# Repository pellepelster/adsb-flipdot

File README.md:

# ADS-B FlipDot

As an avid aviation nerd who happens to live almost exactly on the extended centerline of EDDH's RWY 15, I have a
constant stream of airplanes flying over my house. And although EDDH is a small airport that is rarely visited by
exciting aircraft, I still often step outside when I hear a plane approaching to see what is coming.

I am also a nerd and fully aware of apps like Flightradar24, but I wanted a dedicated device to show me what's flying
overhead, one that gives off some airport vibes instead of a boring mobile phone screen.

https://github.com/user-attachments/assets/cd77bf14-a6f2-4459-a4ed-02358a0cf8c3

## The plan

### ADS-B data

I do not want to rely on or pay for an API to run the displays. The data that Flightradar24 is based on can be received<video src="video/adsb-flipdot-video-embedded.mp4" controls muted playsinline width="100%"></video>
freely using an RTL2832U-based DVB-T stick, which can be tuned far beyond the standard television bands, up to
1090 MHz, to receive the ADS-B data the aircraft are broadcasting.

Looking into the [ADS-B message structure](https://mode-s.org/1090mhz/index.html), the most important information for
my use case is the current position as latitude and longitude, as well as the current heading and altitude.

Using this information I can create a virtual box around my house, catching all aircraft that cross this box at a
certain altitude and filtering out all other irrelevant traffic that is crossing overhead.

### Display

In an ideal world I would like to use a [split-flap](https://en.wikipedia.org/wiki/Split-flap_display) display like the
ones that were widely used at airports (some, e.g. EDDF, still have them). Looking at the prices for original modules
or even DIY alternatives, those are completely out of my price range for this project.

Luckily, the technology that replaced them is much more accessible.
[Flip-disc (or flip-dot)](https://en.wikipedia.org/wiki/Flip-disc_display) displays not only make a nice clicking noise
resembling that of split-flap displays, they can also show arbitrary glyphs. They were widely used as destination signs
in buses and are thus readily available on second-hand platforms.

### Processing

Because the data from ADS-B comes in via USB and needs a bit of processing power and driving the matrix display requires
quite a few I/O lines to address and drive the dots, a old Raspberry PI is a perfect fit for the task. I also wanted to
use this opportunity to get to know Rust a little bit closer, and there is a
nice [crate](https://docs.rs/rs1090/latest/rs1090/)
available that already can decode ADS-B messages.

## Implementation

### Display

#### The dots

The Mobitec is built from an array of small hinged discs with different colors on each side, that show as black or
yellow forming the dots.

The displays are chainable (up to 6 i Think). To understand how to drive them correctly without risking damage, we need to 
look a little bit deeper into how they work internally.

Each disc carries a small bar magnet along its length and sits above the two poles of a U-shaped iron core with a
coil wound around it. A short current pulse through the coil magnetises the core. Its poles pull the opposite ends of
the disc magnet, and the disc turns until each end of the magnet faces the opposite pole. Reversing the current swaps
the poles, and the disc turns half a turn to show its other face. After the pulse the disc magnet holds on to the iron
core, so the disc keeps its position without power and the coil only needs a short pulse to flip it.

The Mobitec has an 26 pin input header, allows to select each individual dot, and also to turn it back and forth.

#### Dot selection

A dot is picked by two 5 bit addresses, one for the row (pins 5, 7, 6, 8 and 9) and one for the column (pins 13 to
17). The panel does not decode them as plain numbers. The two upper bits pick one of several decoder chips, each of
which drives a group of seven lines, and the three lower bits pick one line of that group. A value of 0 in the lower
bits selects nothing, so every eighth address (0, 8, 16, 24) is skipped:

| Rows  | Address | Columns | Address |
|-------|---------|---------|---------|
| 1–7   | 1–7     | 1–7     | 1–7     |
| 8–14  | 9–15    | 8–14    | 9–15    |
| 15–16 | 17–18   | 15–21   | 17–23   |
|       |         | 22–28   | 25–31   |

For example, the dot in row 10, column 20:

|        | Number | Group | Line | Address    | Pins high  | Pins low |
|--------|--------|-------|------|------------|------------|----------|
| Row    | 10     | 1     | 3    | 11 = 01011 | 5, 7, 8    | 6, 9     |
| Column | 20     | 2     | 6    | 22 = 10110 | 14, 15, 17 | 13, 16   |

#### Flipping a dot

Once a dot is selected, three more signals decide what happens to it. Each row has two lines, one that can only feed
current into its coils and one that can only drain it, separated by a diode at every dot. The column has a single line
that can be connected to the coil supply or to ground.

- **Direction (pin 18)** picks which way the current runs through the coil. Low connects the row to the coil supply
  and the column to ground, and the dot turns yellow. High does the opposite, and the dot turns black.
- **Row enable (pin 11 ROW-LOW, pin 10 ROW-HIGH)** switches the row side on. Use pin 11 together with pin 18 low and
  pin 10 together with pin 18 high, and never set both at the same time.
- **Select (pin 19)** fires the dot. Current only flows while it is high, so a pulse of about 190 µs flips the dot.
  Keep it short: a coil that stays energised overheats.

So one dot is flipped in four steps: set the address and the direction, enable the row, pulse pin 19 and switch the
row off again before the next dot.

### Raspberry HAT

Dot selection and configuration of the flipping direction expects 5v logic, and although the Raspberry Pi has plenty of GPIO pins, they all only deliver 3.3v. To be able to drive the display via Raspberry Pi I designed small adapter HAT, that runs the GPIO pins through some levels shifters to deliver the correct 5v. 

All needed design files to manufacture the board are under `./pcb`. Once populated with three levels shifters and a few capacitators to smooth out the current when selecting and switching dots (see BOM at [flipdot-hat-assembly-bom.csv](pcb/assembly/flipdot-hat-assembly-bom.csv)) the HAT can be directly stacked on the Raspberry Pi GPIO pins, and connected to the display via a ribbon cable.

### Software

The software `adsb-flipdot` uses a virtual double-buffered Matrix display. Once new content is written the virtual display computes the diff on yellow/black dots from the previous content to avoid re-drawing the full matrix every time, which would be too time consuming. When no display is attached, the virtual display is written to the console to enable easier debugging.

```shell
./adsb-flipdot debug

Diagnostic tools

Usage: adsb-flipdot debug <COMMAND>

Commands:
  dump       Print every received Mode S / ADS-B frame to the console
  record     Save every received frame to a JSON lines file, for replay with --device-record-file
  all        Show a continuously updated table with one row per aircraft
  filter     Show aircraft passing a rectangle around a point, below an altitude
  flipdot    Preview text as dots, the way the flipdot panel will show it
  pi         Switch the signals of the adapter board on the Raspberry Pi by hand
  clear      Turn every dot of the panels to its dark side
  pattern    Show test patterns one after another, until stopped
  templates  List the codes that can be used in `live --template`
  help       Print this message or the help of the given subcommand(s)
```

The default lat/long parameters are tuned so the flight info is shown once the aircraft passes my house, this is how it looks in real life

https://github.com/user-attachments/assets/cd77bf14-a6f2-4459-a4ed-02358a0cf8c3

## Building and deploying

All tasks to build and deploy solutions are documented and executable via [mise](https://mise.jdx.dev)

```shell
 mise t
Name           Description
ansible        Set up a Raspberry Pi over SSH (udev rule + DVB blacklist), e.g. `mise ansible 10.42.0.112`
build          Build the project (debug)
build:pi       Cross-compile static release binaries for 64-bit and 32-bit Raspberry Pi (needs Docker)
build:pi:32    Cross-compile a static release binary for 32-bit Raspberry Pi, e.g. the Pi 2 (needs Docker)
build:pi:64    Cross-compile a static release binary for 64-bit Raspberry Pi (needs Docker)
check          Format check + clippy + tests
clean          Remove build artifacts
fmt            Format sources
fmt:check      Verify formatting
lint           Run clippy with warnings as errors
pcb:board      Place, autoroute and pour the board (build_board.py -> .kicad_pcb)
pcb:drc        Run DRC (-> pcb/drc.json)
pcb:generate   Regenerate all generated PCB files (board, DRC, gerbers, assembly, renders)
pcb:gerbers    Export gerbers and drill files (-> pcb/gerbers/)
pcb:placement  Export the placement file (-> pcb/assembly/)
pcb:render     Render pcb/top.png and pcb/bottom.png
pcb:zip        Pack pcb/gerbers/ and pcb/assembly/ into the upload zips
release        Build the project (release)
run            Run adsb-flipdot (release build), e.g. `mise run run debug dump`
setup-udev     Install udev rule + DVB blacklist for the RTL2832U dongle (needs sudo)
test           Run tests
```

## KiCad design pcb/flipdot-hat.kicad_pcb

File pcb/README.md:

# Flip-dot adapter board

A Raspberry Pi HAT that connects the Pi to the 26-pin header of a Mobitec
flip-dot panel. The board is generated by `build_board.py`.

The signals, the panel pinout, the addresses and how to switch a dot are
described in [docs/mobitec/README.md](../docs/mobitec/README.md).

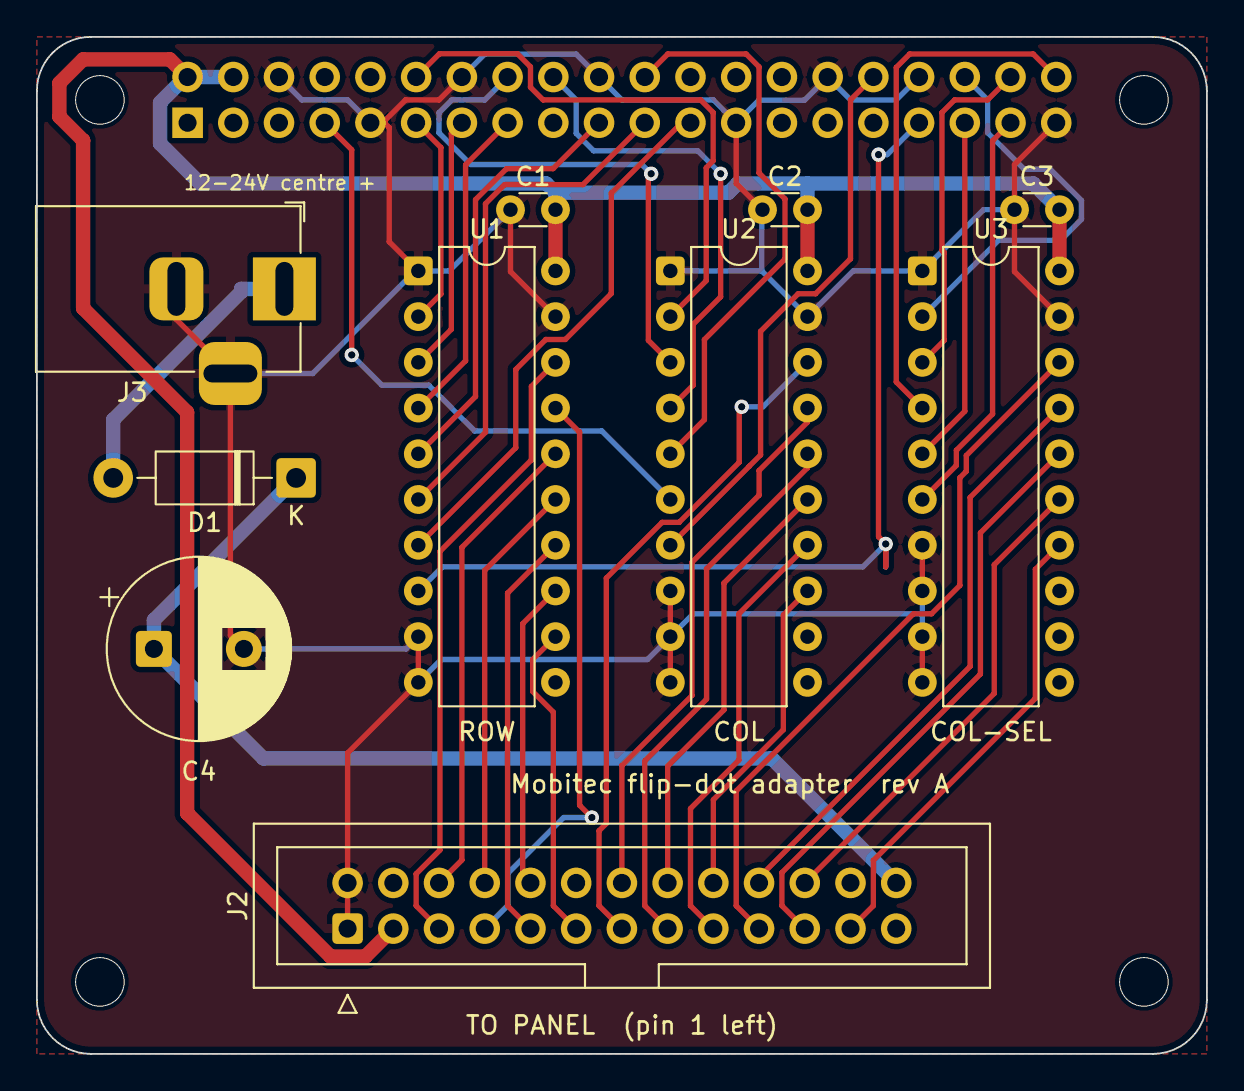
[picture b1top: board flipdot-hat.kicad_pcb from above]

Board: 2 copper layers, 65.0 x 56.5 mm, 15 parts (1 on the bottom side), 40 nets.

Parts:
C1, C2, C3: 100n; C_Disc_D3.0mm_W1.6mm_P2.50mm
C4: 470u 35V; CP_Radial_D10.0mm_P5.00mm
D1: 1N5819; D_DO-41_SOD81_P10.16mm_Horizontal
H1, H2, H3, H4: M2.5; MountingHole_2.7mm_M2.5
J1: Pi socket 2x20; PinSocket_2x20_P2.54mm_Vertical
J2: Panel 2x13 IDC; IDC-Header_2x13_P2.54mm_Vertical
J3: 12-24V 5.5x2.1 centre +; BarrelJack_Horizontal
U1, U2, U3: 74HCT541; DIP-20_W7.62mm

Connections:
+5V: C1.1, C2.1, C3.1, J1.2, J1.4, J2.3, U1.20, U2.20, U3.20
+12V: C4.1, D1.1, J2.26
COL0: J2.13, U2.18
COL1: J2.14, U2.17
COL2: J2.15, U2.16
COL3: J2.16, U2.15
COL4: J2.17, U2.14
COL-H/L: J2.18, U2.13
COL-SEL0: J2.19, U3.18
COL-SEL1: J2.20, U3.17
COL-SEL2: J2.21, U3.16
COL-SEL3: J2.22, U3.15
COL-SEL4: J2.23, U3.14
GND: C1.2, C2.2, C3.2, C4.2, J1.6, J1.9, J1.14, J1.20, J1.25, J1.30, J1.34, J1.39, J2.1, J2.2, J3.2, J3.3, U1.1, U1.9, U1.10, U1.19, U2.1, U2.8, U2.9, U2.10, U2.19, U3.1, U3.7, U3.8, U3.9, U3.10, U3.19
PI_COL0: J1.12, U2.2
PI_COL1: J1.16, U2.3
PI_COL2: J1.18, U2.4
PI_COL3: J1.22, U2.5
PI_COL4: J1.7, U2.6
PI_COL-H/L: J1.32, U2.7
PI_COL-SEL0: J1.36, U3.2
PI_COL-SEL1: J1.38, U3.3
PI_COL-SEL2: J1.40, U3.4
PI_COL-SEL3: J1.35, U3.5
PI_COL-SEL4: J1.37, U3.6
PI_ROW0: J1.11, U1.2
PI_ROW1: J1.13, U1.3
PI_ROW2: J1.15, U1.4
PI_ROW3: J1.19, U1.5
PI_ROW4: J1.21, U1.6
PI_ROW-HIGH: J1.23, U1.7
PI_ROW-LOW: J1.33, U1.8
ROW0: J2.5, U1.18
ROW1: J2.7, U1.17
ROW2: J2.6, U1.16
ROW3: J2.8, U1.15
ROW4: J2.9, U1.14
ROW-HIGH: J2.10, U1.13
ROW-LOW: J2.11, U1.12
VIN: D1.2, J3.1

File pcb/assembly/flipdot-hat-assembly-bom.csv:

Item #,Designator,Qty,Manufacturer,Mfg Part #,Description / Value,Package / Footprint,Type,Notes
1,"U1,U2,U3",3,Texas Instruments,SN74HCT541N,Octal buffer 74HCT541,DIP-20,THT,Solder directly (no sockets)
2,"C1,C2,C3",3,Vishay,K104K15X7RF53L2,100 nF 50 V X7R ceramic,Radial 2.5 mm pitch,THT,Any equivalent accepted
3,C4,1,Panasonic,EEU-FR1V471,470 uF 35 V electrolytic,Radial 10 mm dia / 5 mm pitch,THT,Observe polarity; any equivalent accepted
4,D1,1,onsemi,1N5819,Schottky diode 40 V 1 A,DO-41,THT,Cathode band to square pad
5,J1,1,Samtec,SSW-120-01-T-D,2x20 female socket 2.54 mm,Through-hole vertical,THT,MOUNT ON BOTTOM SIDE; any equivalent with 8.5 mm body accepted
6,J2,1,Wurth Elektronik,61202621621,2x13 shrouded box header 2.54 mm,Through-hole vertical,THT,Notch toward board edge as on silkscreen
7,J3,1,CUI Devices,PJ-102A,DC barrel jack 5.5 x 2.1 mm,DC-005 style through-hole,THT,Check fit against footprint before purchase; equivalent DC-005 accepted

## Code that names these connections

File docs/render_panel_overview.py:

#!/usr/bin/env python3
"""Draw docs/mobitec/panel-overview.svg: the groups of header pins, the row and
column decoders as blocks and the dot matrix they drive.

    python3 docs/render_panel_overview.py
    google-chrome --headless --screenshot=docs/mobitec/panel-overview.png \
        --window-size=1640,1010 --force-device-scale-factor=1.25 docs/mobitec/panel-overview.svg
"""
from pathlib import Path

from diagram import *  # noqa: F401,F403

W, H = 1640, 1010
ROWC, COLC, ENC, DIRC, SELC = C_ROW, C_COL, C_DRV, C_DIR, C_SEL
YEL = "#facc15"




text(40, 46, "Mobitec panel: from header pins to dots", 26, weight="bold")
text(40, 72, "One 28 × 16 panel. What each group of input pins does; the decoders and drivers on the panel are drawn as blocks.",
     14, fill="#4b5563")

# ---------- header ----------
HX, HY, HW = 40, 110, 300
groups = [
    ("Row address", "pins 5, 7, 6, 8, 9", "ROW0–ROW4", ROWC, 150),
    ("Row enable", "pins 10, 11", "ROW-HIGH, ROW-LOW", ENC, 270),
    ("Column address", "pins 13–17", "COL0–COL4", COLC, 550),
    ("Direction", "pin 18", "COL-H/L", DIRC, 660),
    ("Select (fire)", "pin 19", "COL-SEL0", SELC, 760),
]
rect(HX, HY, HW, 770, "#fefce8", "#854d0e")
text(HX + 14, HY + 26, "26-pin header", 16, weight="bold", fill="#854d0e")
for name, pins, sigs, color, y in groups:
    rect(HX + 12, y - 26, HW - 24, 62, "#fff", color, 6, 2)
    text(HX + 26, y - 4, name, 14, weight="bold", fill=color)
    text(HX + 26, y + 16, pins, 13)
    text(HX + HW - 26, y + 16, sigs, 11.5, "end", fill=GREY, mono=True)
y = 835
for s in ("pins 1, 2 GND · 3 +5 V · 26 coil supply",
          "pins 20–24: select of the next panels"):
    text(HX + 14, y, s, 11.5, fill=GREY)
    y += 18

# ---------- matrix ----------
MX, MY, P = 900, 150, 24
NC, NR = 28, 16
R_SEL, C_SEL_ = 3, 8          # example dot
rect(MX - 16, MY - 16, NC * P + 8, NR * P + 8, "#111827", "#111827", 6)
for r in range(NR):
    for c in range(NC):
        on = (r, c) == (R_SEL - 1, C_SEL_ - 1)
        hl = r == R_SEL - 1 or c == C_SEL_ - 1
        out.append('<circle cx="%g" cy="%g" r="%g" fill="%s" stroke="%s" stroke-width="%g"/>' % (
            MX + c * P, MY + r * P, 8.5, YEL if on else ("#374151" if hl else "#1f2937"),
            "#fff" if on else ("#6b7280" if hl else "#374151"), 3 if on else 1.2))
line(MX - 16, MY + (R_SEL - 1) * P, MX + NC * P - 8, MY + (R_SEL - 1) * P, ROWC, 2)
line(MX + (C_SEL_ - 1) * P, MY - 16, MX + (C_SEL_ - 1) * P, MY + NR * P - 8, COLC, 2)
for r in (1, 8, 16):
    text(MX + NC * P + 2, MY + (r - 1) * P + 4, "row %d" % r, 11, fill=GREY)
for c in (1, 8, 15, 22, 28):
    text(MX + (c - 1) * P, MY - 24, str(c), 11, "middle", fill=GREY)
text(MX + NC * P / 2 - 8, MY - 42, "columns", 12, "middle", fill=GREY)

# ---------- row side ----------
RDX = 640
rect(RDX, MY - 16, 200, NR * P + 8, "#eff6ff", ROWC, 8, 2)
text(RDX + 100, MY + 40, "Row decoder", 15, "middle", weight="bold", fill=ROWC)
text(RDX + 100, MY + 60, "+ row drivers", 13, "middle", fill=ROWC)
for i, s in enumerate(("Picks 1 of 16 rows:", "address 1–7 → rows 1–7", "9–15 → rows 8–14",
                       "17, 18 → rows 15, 16", "", "On only while pin 10", "or pin 11 is high")):
    text(RDX + 100, MY + 100 + i * 19, s, 12, "middle")
arrow(RDX + 200, MY + (R_SEL - 1) * P, MX - 18, MY + (R_SEL - 1) * P, ROWC, 3)
for r in range(NR):
    line(RDX + 200, MY + r * P, RDX + 214, MY + r * P, ROWC, 1.5)

# ---------- column side ----------
CDY = MY + NR * P + 60
rect(MX - 16, CDY, NC * P + 8, 150, "#f0fdf4", COLC, 8, 2)
text(MX + NC * P / 2 - 8, CDY + 28, "Column decoder + column drivers", 15, "middle", weight="bold", fill=COLC)
for i, s in enumerate(("Picks 1 of 28 columns: address 1–7 → columns 1–7, 9–15 → 8–14,",
                       "17–23 → 15–21, 25–31 → 22–28. Addresses 0, 8, 16, 24 pick nothing.",
                       "On only for the moment pin 19 rises: that pulse is what flips the dot.")):
    text(MX + NC * P / 2 - 8, CDY + 56 + i * 20, s, 12, "middle")
arrow(MX + (C_SEL_ - 1) * P, CDY, MX + (C_SEL_ - 1) * P, MY + NR * P - 6, COLC, 3)
for c in range(NC):
    line(MX + c * P, CDY, MX + c * P, CDY - 12, COLC, 1.5)

# ---------- wires from the header ----------
def route(y, color, pts, w=3):
    poly([(HX + HW - 12, y)] + pts, color, w)


route(groups[0][4], ROWC, [(560, groups[0][4]), (560, MY + 60), (RDX, MY + 60)])
arrow(560, MY + 60, RDX, MY + 60, ROWC)
route(groups[1][4], ENC, [(580, groups[1][4]), (580, MY + 300), (RDX - 2, MY + 300)])
arrow(580, MY + 300, RDX, MY + 300, ENC)
route(groups[2][4], COLC, [(MX - 120, groups[2][4]), (MX - 120, CDY + 40)])
arrow(MX - 120, CDY + 40, MX - 16, CDY + 40, COLC)
route(groups[4][4], SELC, [(MX - 80, groups[4][4]), (MX - 80, CDY + 110)])
arrow(MX - 80, CDY + 110, MX - 16, CDY + 110, SELC)
# direction goes to both
yd = groups[3][4]
route(yd, DIRC, [(520, yd)])
poly([(520, yd), (520, MY + 340), (RDX, MY + 340)], DIRC, 3)
arrow(520, MY + 340, RDX, MY + 340, DIRC)
poly([(520, yd), (MX - 100, yd), (MX - 100, CDY + 75)], DIRC, 3)
arrow(MX - 100, CDY + 75, MX - 16, CDY + 75, DIRC)
dot(520, yd, DIRC, 5)
text(540, yd + 26, "Direction goes to both decoders:", 12, weight="bold", fill=DIRC)
text(540, yd + 42, "it sets which way the current", 12, fill=DIRC)
text(540, yd + 58, "runs through the coil", 12, fill=DIRC)

# ---------- example and colours ----------
ex, ey = 380, 830
rect(ex - 10, ey - 24, 270, 116, "#fff", "#d1d5db", 6, 1.2)
text(ex, ey, "Example (the yellow dot)", 13, weight="bold")
for i, s in enumerate(("row address 3 → row 3", "column address 9 → column 8",
                       "ROW-LOW, pin 18 low → yellow", "ROW-HIGH, pin 18 high → black", "then one pulse on pin 19")):
    text(ex, ey + 20 + i * 17, s, 12)
text(MX - 16, CDY + 186, "Colours measured on our panel: pin 18 low with ROW-LOW shows yellow, pin 18 high with ROW-HIGH black.",
     11.5, fill=GREY)

bx, by = MX - 16, CDY + 214
rect(bx, by, NC * P + 8, 150, "#faf5ff", ENC, 8, 1.5)
text(bx + 16, by + 26, "ROW-HIGH and ROW-LOW (pins 10, 11)", 14, weight="bold", fill=ENC)
for i, s_ in enumerate((
        "On our panel both pins go into one NOR gate that switches the row decoder on. Either one high is",
        "enough, and both do the same: the direction of the current comes from pin 18 alone.",
        "The names come from older Mobitec panels with FP2800 drivers. There ROW-HIGH connects the row",
        "to the coil supply and ROW-LOW connects it to ground, and both high together shorts the supply.",
        "Drive them the way that suits both: ROW-LOW with pin 18 low, ROW-HIGH with pin 18 high, never both.")):
    text(bx + 16, by + 50 + i * 19, s_, 12, fill="#374151")

save(Path(__file__).parent / "mobitec" / "panel-overview.svg", W, H)

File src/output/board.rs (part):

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    fn a_failed_flip_drives_every_line_low() {
        let (mut board, _log) = board();
        board.flip(0, 1, 1, true).unwrap();
        board.pins.broken = Some(gpio("COL1"));
        assert!(board.flip(0, 1, 2, true).is_err());
        assert!(board.levels.iter().all(|high| !high));
        assert_eq!(board.pulses, 1, "no pulse for the failed flip");
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        assert!(board.levels[index("COL2")]);
        board.press(index("COL2")).unwrap();
        assert!(!board.levels[index("COL2")]);
        assert_eq!(*log.borrow(), [(gpio("COL2"), true), (gpio("COL2"), false)]);
    }

    #[test]
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        let (mut board, log) = board();
        board.press(index("ROW0")).unwrap();
        board.press(index("COL4")).unwrap();
        board.pins.broken = Some(gpio("ROW0"));
        log.borrow_mut().clear();

        assert!(board.all_low().is_err());
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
